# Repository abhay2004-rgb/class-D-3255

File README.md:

# class-D-3255
High-performance Class-D audio amplifier project based on the TPA3255 IC, designed for efficient power amplification, high-quality sound reproduction, and low distortion. This project explores audio electronics, amplifier integration, and DIY speaker system development.

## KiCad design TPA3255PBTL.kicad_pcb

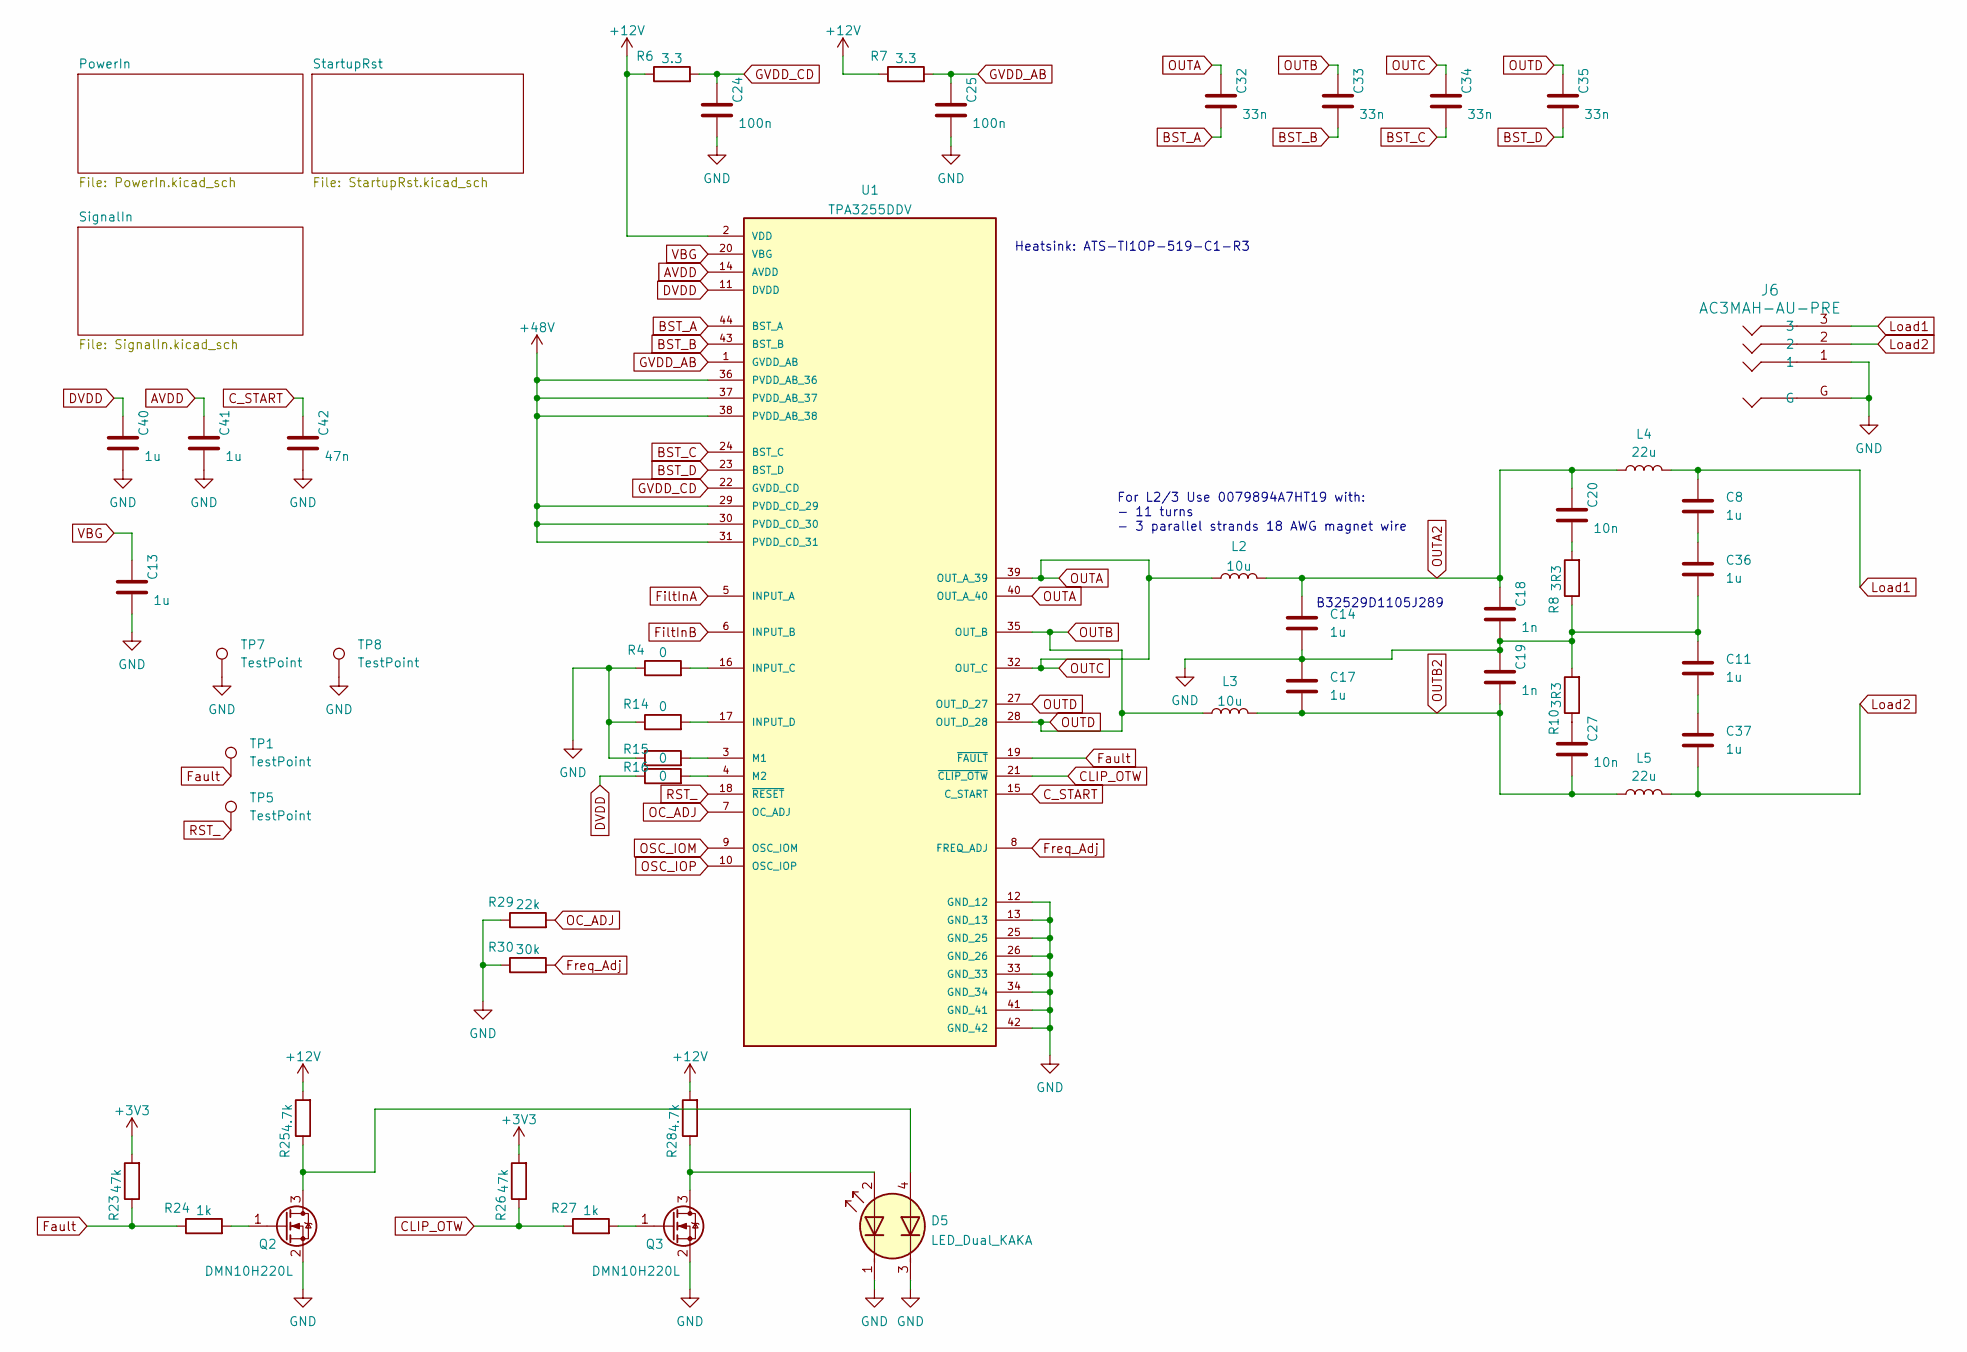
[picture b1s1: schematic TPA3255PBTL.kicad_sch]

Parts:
C8, C11, C14, C17, C36, C37: 1u; C_Rect_L7.2mm_W7.2mm_P5.00mm_FKS2_FKP2_MKS2_MKP2
C13, C40, C41: 1u; C_0805_2012Metric
C18, C19: 1n; C_0805_2012Metric
C20, C27: 10n; C_0805_2012Metric
C24, C25: 100n; C_0805_2012Metric
C32, C33, C34, C35: 33n; C_0805_2012Metric
C42: 47n; C_0805_2012Metric
D5: LED_Dual_KAKA; IC4_WP934EB_2GD_KNB
J6: AC3MAH-AU-PRE; AC3MAH-AU-PRE_AMP
L2, L3: 10u; L_Toroid_Vertical_L22.4mm_W10.2mm_P7.90mm_Vishay_TJ4
L4, L5: 22u; L_Toroid_Vertical_L22.4mm_W10.2mm_P7.90mm_Vishay_TJ4
Q2, Q3: DMN10H220L; SOT-23
R4, R14, R15, R16: 0; R_0805_2012Metric
R6, R7: 3.3; R_0805_2012Metric
R8, R10: 3R3; R_0805_2012Metric
R23, R26: 47k; R_0805_2012Metric
R24, R27: 1k; R_0805_2012Metric
R25, R28: 4.7k; R_0805_2012Metric
R29: 22k; R_0805_2012Metric
R30: 30k; R_0805_2012Metric
TP1, TP5, TP7, TP8: TestPoint; TestPoint_THTPad_1.0x1.0mm_Drill0.5mm
U1: TPA3255DDV; SOP63P810X120-44N; PARTREV A

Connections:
+3V3: R23.2, R26.2; also elsewhere on the board
+12V: R6.1, R7.1, R25.2, R28.2, U1.2 (VDD); also elsewhere on the board
+48V: U1.29 (PVDD_CD_29), U1.30 (PVDD_CD_30), U1.31 (PVDD_CD_31), U1.36 (PVDD_AB_36), U1.37 (PVDD_AB_37), U1.38 (PVDD_AB_38); also elsewhere on the board
AVDD: C41.1, U1.14 (AVDD)
BST_A: C32.2, U1.44 (BST_A)
BST_B: C33.2, U1.43 (BST_B)
BST_C: C34.2, U1.24 (BST_C)
BST_D: C35.2, U1.23 (BST_D)
CLIP_OTW: R26.1, R27.1, U1.21 (~CLIP_OTW)
C_START: C42.1, U1.15 (C_START)
DVDD: C40.1, R16.1, U1.11 (DVDD)
Fault: R23.1, R24.1, TP1.1, U1.19 (~FAULT)
FiltInA: U1.5 (INPUT_A); also elsewhere on the board
FiltInB: U1.6 (INPUT_B); also elsewhere on the board
Freq_Adj: R30.2, U1.8 (FREQ_ADJ)
GND: C11.1, C13.2, C14.2, C17.1, C18.2, C19.1, C24.2, C25.2, C36.2, C40.2, C41.2, C42.2, D5.1 (A1), D5.3 (A2), J6.1, J6.G, Q2.2 (S), Q3.2 (S), R4.1, R8.1, R10.2, R14.1, R15.1, R29.1, R30.1, TP7.1, TP8.1, U1.12 (GND_12), U1.13 (GND_13), U1.25 (GND_25), U1.26 (GND_26), U1.33 (GND_33), U1.34 (GND_34), U1.41 (GND_41), U1.42 (GND_42); also elsewhere on the board
GVDD_AB: C25.1, R7.2, U1.1 (GVDD_AB)
GVDD_CD: C24.1, R6.2, U1.22 (GVDD_CD)
Load1: C8.1, J6.3, L4.2; also elsewhere on the board
Load2: C37.2, J6.2, L5.2; also elsewhere on the board
unnamed: C11.2, C37.1
unnamed: C20.2, R8.2
unnamed: C27.1, R10.1
unnamed: C8.2, C36.1
unnamed: D5.2 (K1), Q3.3 (D), R28.1
unnamed: D5.4 (K2), Q2.3 (D), R25.1
unnamed: Q2.1 (G), R24.2
unnamed: Q3.1 (G), R27.2
unnamed: R4.2, U1.16 (INPUT_C)
unnamed: R14.2, U1.17 (INPUT_D)
unnamed: R15.2, U1.3 (M1)
unnamed: R16.2, U1.4 (M2)
OC_ADJ: R29.2, U1.7 (OC_ADJ)
OSC_IOM: U1.9 (OSC_IOM)
OSC_IOP: U1.10 (OSC_IOP)
OUTA: C32.1, C34.1, L2.1, U1.32 (OUT_C), U1.39 (OUT_A_39), U1.40 (OUT_A_40)
OUTA2: C14.1, C18.1, C20.1, L2.2, L4.1
OUTB: C33.1, C35.1, L3.1, U1.27 (OUT_D_27), U1.28 (OUT_D_28), U1.35 (OUT_B)
OUTB2: C17.2, C19.2, C27.2, L3.2, L5.1
RST_: TP5.1, U1.18 (~RESET); also elsewhere on the board
VBG: C13.1, U1.20 (VBG)

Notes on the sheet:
B32529D1105J289
For L2/3 Use 0079894A7HT19 with: - 11 turns - 3 parallel strands 18 AWG magnet wire
Heatsink: ATS-TI1OP-519-C1-R3

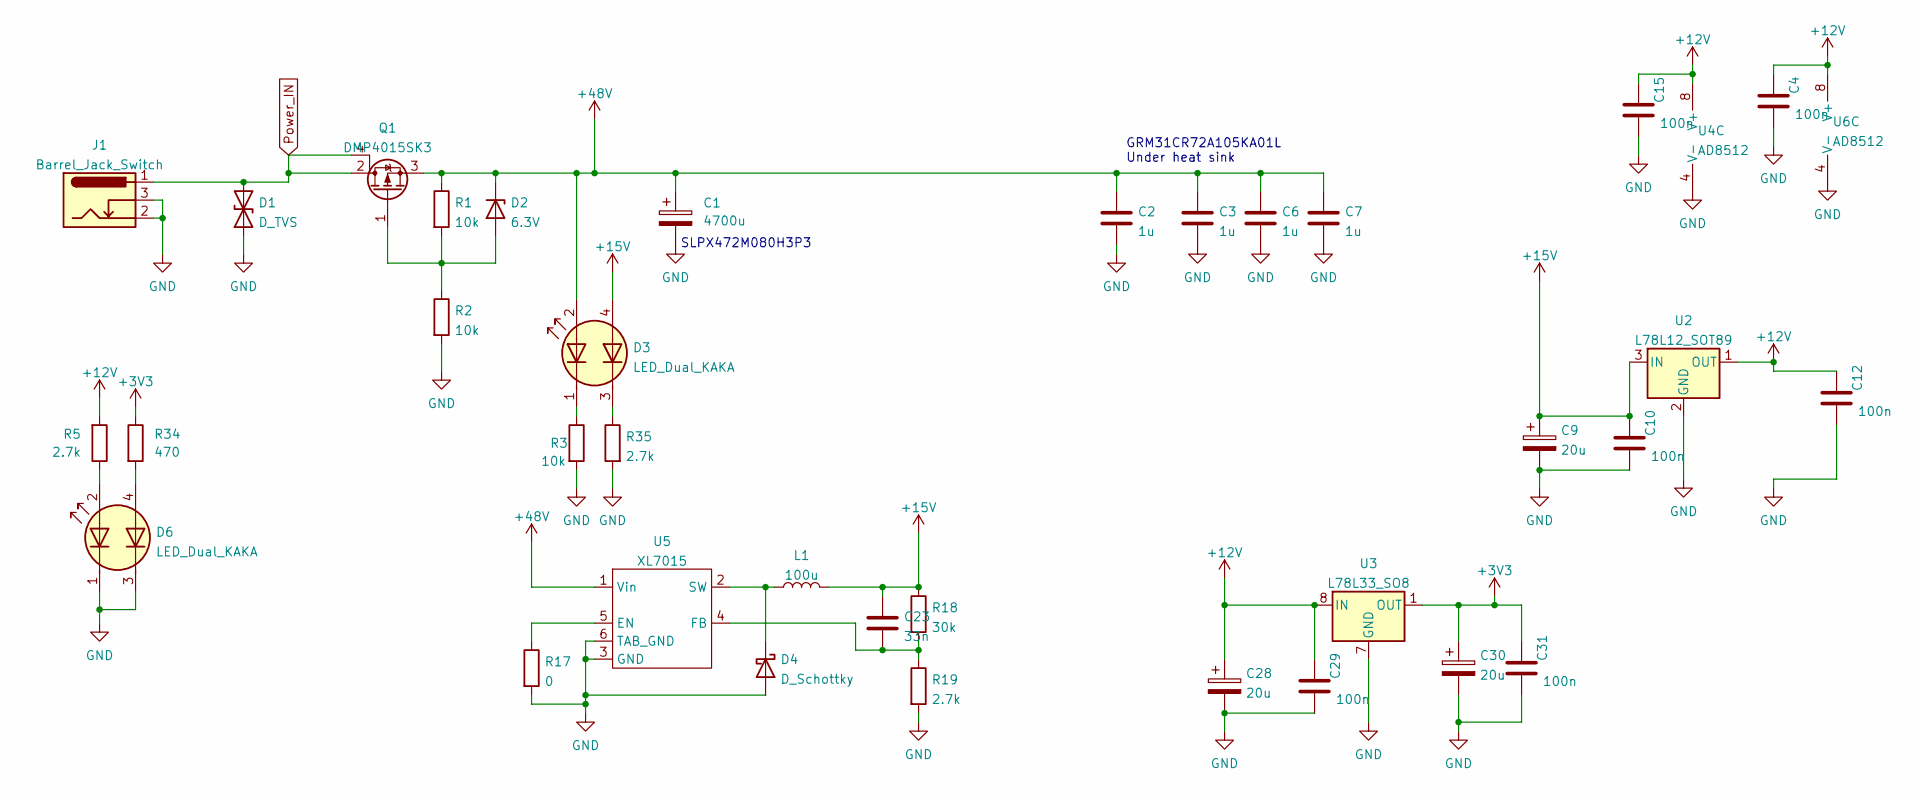
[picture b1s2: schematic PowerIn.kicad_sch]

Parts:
C1: 4700u; CP_Radial_D35.0mm_P10.00mm_SnapIn
C2, C3, C6, C7: 1u; C_1206_3216Metric
C4, C10, C12, C15, C29, C31: 100n; C_0805_2012Metric
C9, C28, C30: 20u; CP_Radial_D6.3mm_P2.50mm
C23: 33n; C_0805_2012Metric
D1: D_TVS; D_SOD-123
D2: 6.3V; D_SOD-123
D3, D6: LED_Dual_KAKA; IC4_WP934EB_2GD_KNB
D4: D_Schottky; D_SOD-123
J1: Barrel_Jack_Switch; BarrelJack_GCT_DCJ200-10-A_Horizontal
L1: 100u; MWPY8040; LCSC C501759
Q1: DMP4015SK3; TO-252-3_TabPin4
R1, R2, R3: 10k; R_0805_2012Metric
R5, R19, R35: 2.7k; R_0805_2012Metric
R17: 0; R_0805_2012Metric
R18: 30k; R_0805_2012Metric
R34: 470; R_0805_2012Metric
U2: L78L12_SOT89; SOT-89-3
U3: L78L33_SO8; SOIC-8_3.9x4.9mm_P1.27mm
U4, U6: AD8512; SO-8_3.9x4.9mm_P1.27mm
U5: XL7015; XL7015E1

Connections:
+3V3: C30.1, C31.1, R34.1, U3.1 (OUT); also elsewhere on the board
+12V: C4.1, C12.1, C15.1, C28.1, C29.1, R5.2, U2.1 (OUT), U3.8 (IN), U4.8 (V+), U6.8 (V+); also elsewhere on the board
+15V: C9.1, C10.1, C23.1, D3.4 (K2), L1.2, R18.1, U2.3 (IN)
+48V: C1.1, C2.1, C3.1, C6.1, C7.1, D2.1 (K), D3.2 (K1), Q1.3 (S), R1.1, U5.1 (Vin); also elsewhere on the board
GND: C1.2, C2.2, C3.2, C4.2, C6.2, C7.2, C9.2, C10.2, C12.2, C15.2, C28.2, C29.2, C30.2, C31.2, D1.1 (A1), D4.2 (A), D6.1 (A1), D6.3 (A2), J1.2, J1.3, R2.2, R3.2, R17.2, R19.2, R35.2, U2.2 (GND), U3.2 (GND), U3.3 (GND), U3.6 (GND), U3.7 (GND), U4.4 (V-), U5.3 (GND), U5.6 (TAB_GND), U6.4 (V-); also elsewhere on the board
unnamed: D2.2 (A), Q1.1 (G), R1.2, R2.1
unnamed: D3.1 (A1), R3.1
unnamed: D3.3 (A2), R35.1
unnamed: D4.1 (K), L1.1, U5.2 (SW)
unnamed: D6.2 (K1), R5.1
unnamed: D6.4 (K2), R34.2
unnamed: R17.1, U5.5 (EN)
unnamed: C23.2, R18.2, R19.1, U5.4 (FB)
Power_IN: D1.2 (A2), J1.1, Q1.2 (D), Q1.4 (D)

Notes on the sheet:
GRM31CR72A105KA01L Under heat sink
SLPX472M080H3P3

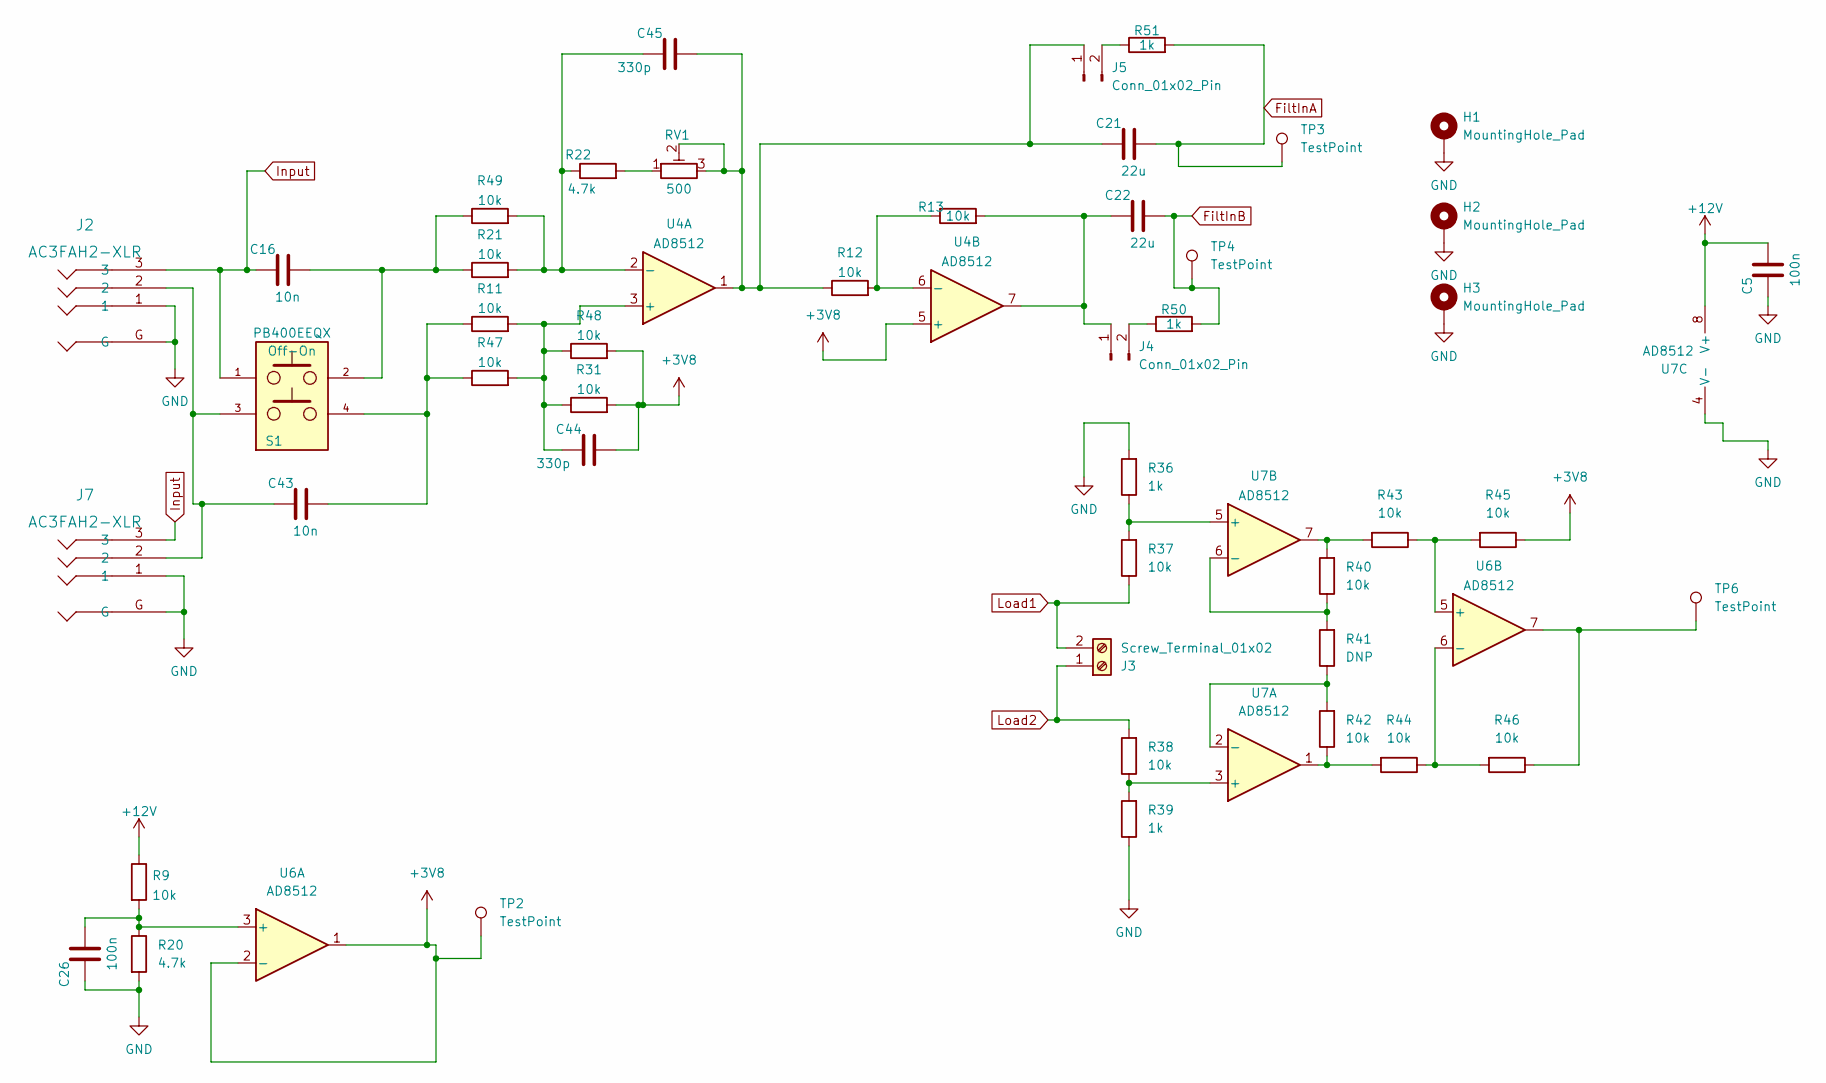
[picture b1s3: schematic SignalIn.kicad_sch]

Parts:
C5, C26: 100n; C_0805_2012Metric
C16, C43: 10n; C_0805_2012Metric
C21, C22: 22u; C_1206_3216Metric_Pad1.33x1.80mm_HandSolder
C44, C45: 330p; C_0805_2012Metric
H1, H2, H3: MountingHole_Pad; MountingHole_3.2mm_M3_Pad_Via
J2, J7: AC3FAH2-XLR; AC3FAH2-F-XLR
J3: Screw_Terminal_01x02; TerminalBlock_Phoenix_MKDS-1,5-2-5.08_1x02_P5.08mm_Horizont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
J4, J5: Conn_01x02_Pin; PinHeader_1x02_P1.27mm_Vertical
R9, R11, R12, R13, R21, R31, R37, R38, R40, R42, R43, R44, R45, R46, R47, R48, R49: 10k; R_0805_2012Metric
R20, R22: 4.7k; R_0805_2012Metric
R36, R39, R50, R51: 1k; R_0805_2012Metric
R41: DNP; R_0805_2012Metric
RV1: 500; Potentiometer_Bourns_3296W_Vertical
S1: PB400EEQX; SW_PB400EEQX; PARTREV NA
TP2, TP3, TP4, TP6: TestPoint; TestPoint_THTPad_1.0x1.0mm_Drill0.5mm
U4, U6, U7: AD8512; SO-8_3.9x4.9mm_P1.27mm

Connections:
+3V8: C44.2, R31.2, R45.1, R48.2, TP2.1, U4.5 (+), U6.1, U6.2 (-)
+12V: C5.2, R9.1, U7.8 (V+); also elsewhere on the board
FiltInA: C21.2, R51.2, TP3.1; also elsewhere on the board
FiltInB: C22.2, R50.2, TP4.1; also elsewhere on the board
GND: C5.1, C26.1, H1.1, H2.1, H3.1, J2.1, J2.G, J7.1, J7.G, R20.2, R36.2, R39.1, U7.4 (V-); also elsewhere on the board
Input: C16.1, J2.3, J7.3, S1.1
Load1: J3.2, R37.1; also elsewhere on the board
Load2: J3.1, R38.2; also elsewhere on the board
unnamed: C16.2, R21.1, R49.1, S1.2
unnamed: C43.1, J2.2, J7.2, S1.3
unnamed: C43.2, R11.1, R47.1, S1.4
unnamed: C22.1, J4.1, R13.2, U4.7
unnamed: J4.2, R50.1
unnamed: C21.1, C45.2, J5.1, R12.1, RV1.2, RV1.3, U4.1
unnamed: J5.2, R51.1
unnamed: R22.2, RV1.1
unnamed: R40.2, R43.2, U7.7
unnamed: R42.1, R44.2, U7.1
unnamed: R46.1, TP6.1, U6.7
unnamed: C44.1, R11.2, R31.1, R47.2, R48.1, U4.3 (+)
unnamed: C45.1, R21.2, R22.1, R49.2, U4.2 (-)
unnamed: R12.2, R13.1, U4.6 (-)
unnamed: C26.2, R9.2, R20.1, U6.3 (+)
unnamed: R43.1, R45.2, U6.5 (+)
unnamed: R44.1, R46.2, U6.6 (-)
unnamed: R38.1, R39.2, U7.3 (+)
unnamed: R41.1, R42.2, U7.2 (-)
unnamed: R36.1, R37.2, U7.5 (+)
unnamed: R40.1, R41.2, U7.6 (-)

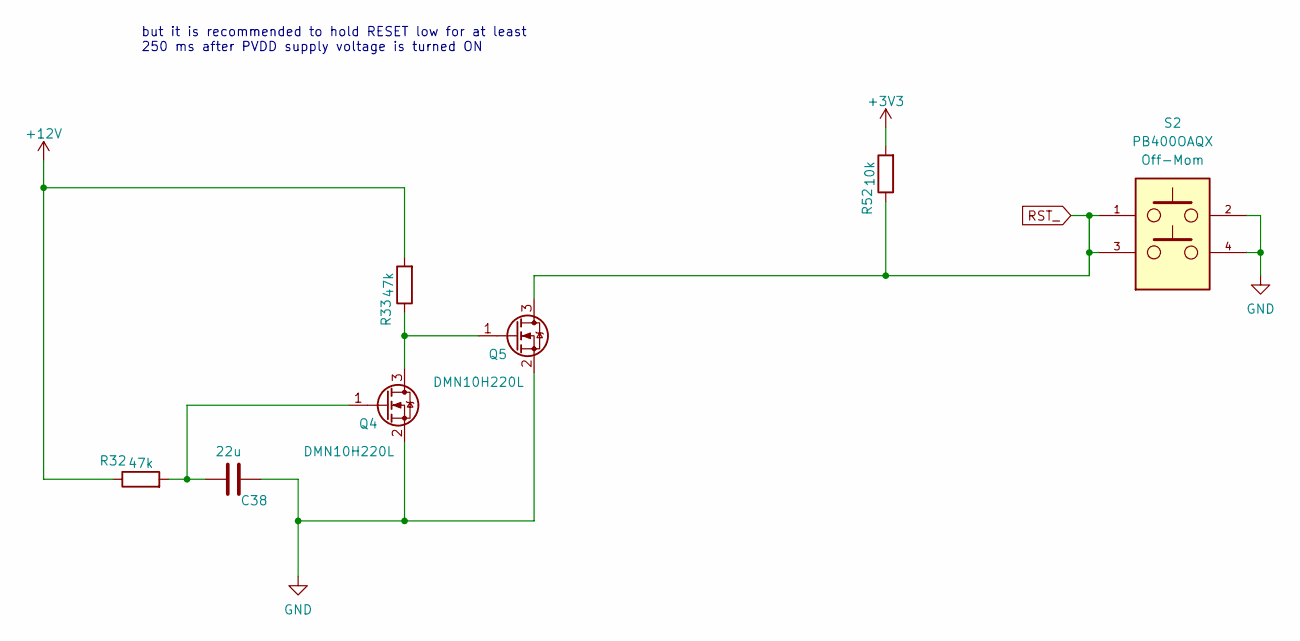
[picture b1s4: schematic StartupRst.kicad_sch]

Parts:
C38: 22u; C_1206_3216Metric_Pad1.33x1.80mm_HandSolder
Q4, Q5: DMN10H220L; SOT-23
R32, R33: 47k; R_0805_2012Metric
R52: 10k; R_0805_2012Metric
S2: PB400OAQX; SW_PB400EEQX; PARTREV NA

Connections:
+3V3: R52.2; also elsewhere on the board
+12V: R32.1, R33.2; also elsewhere on the board
GND: C38.1, Q4.2 (S), Q5.2 (S), S2.2, S2.4; also elsewhere on the board
unnamed: Q4.3 (D), Q5.1 (G), R33.1
unnamed: C38.2, Q4.1 (G), R32.2
RST_: Q5.3 (D), R52.1, S2.1, S2.3; also elsewhere on the board

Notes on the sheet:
but it is recommended to hold RESET low for at least 250 ms after PVDD supply voltage is turned ON

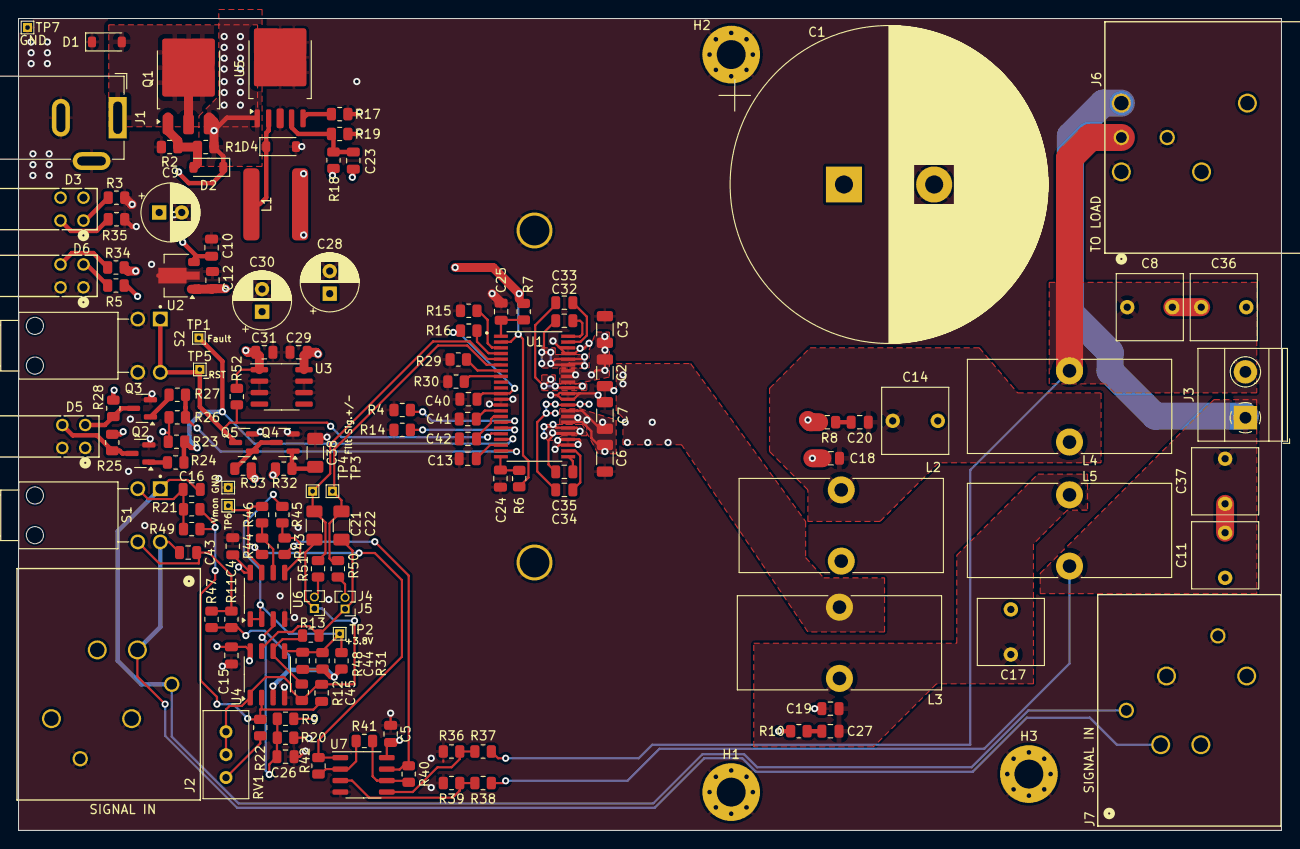
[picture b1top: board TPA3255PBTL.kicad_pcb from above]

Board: 4 copper layers, 140.0 x 90.0 mm, 140 parts (0 on the bottom side), 74 nets.
